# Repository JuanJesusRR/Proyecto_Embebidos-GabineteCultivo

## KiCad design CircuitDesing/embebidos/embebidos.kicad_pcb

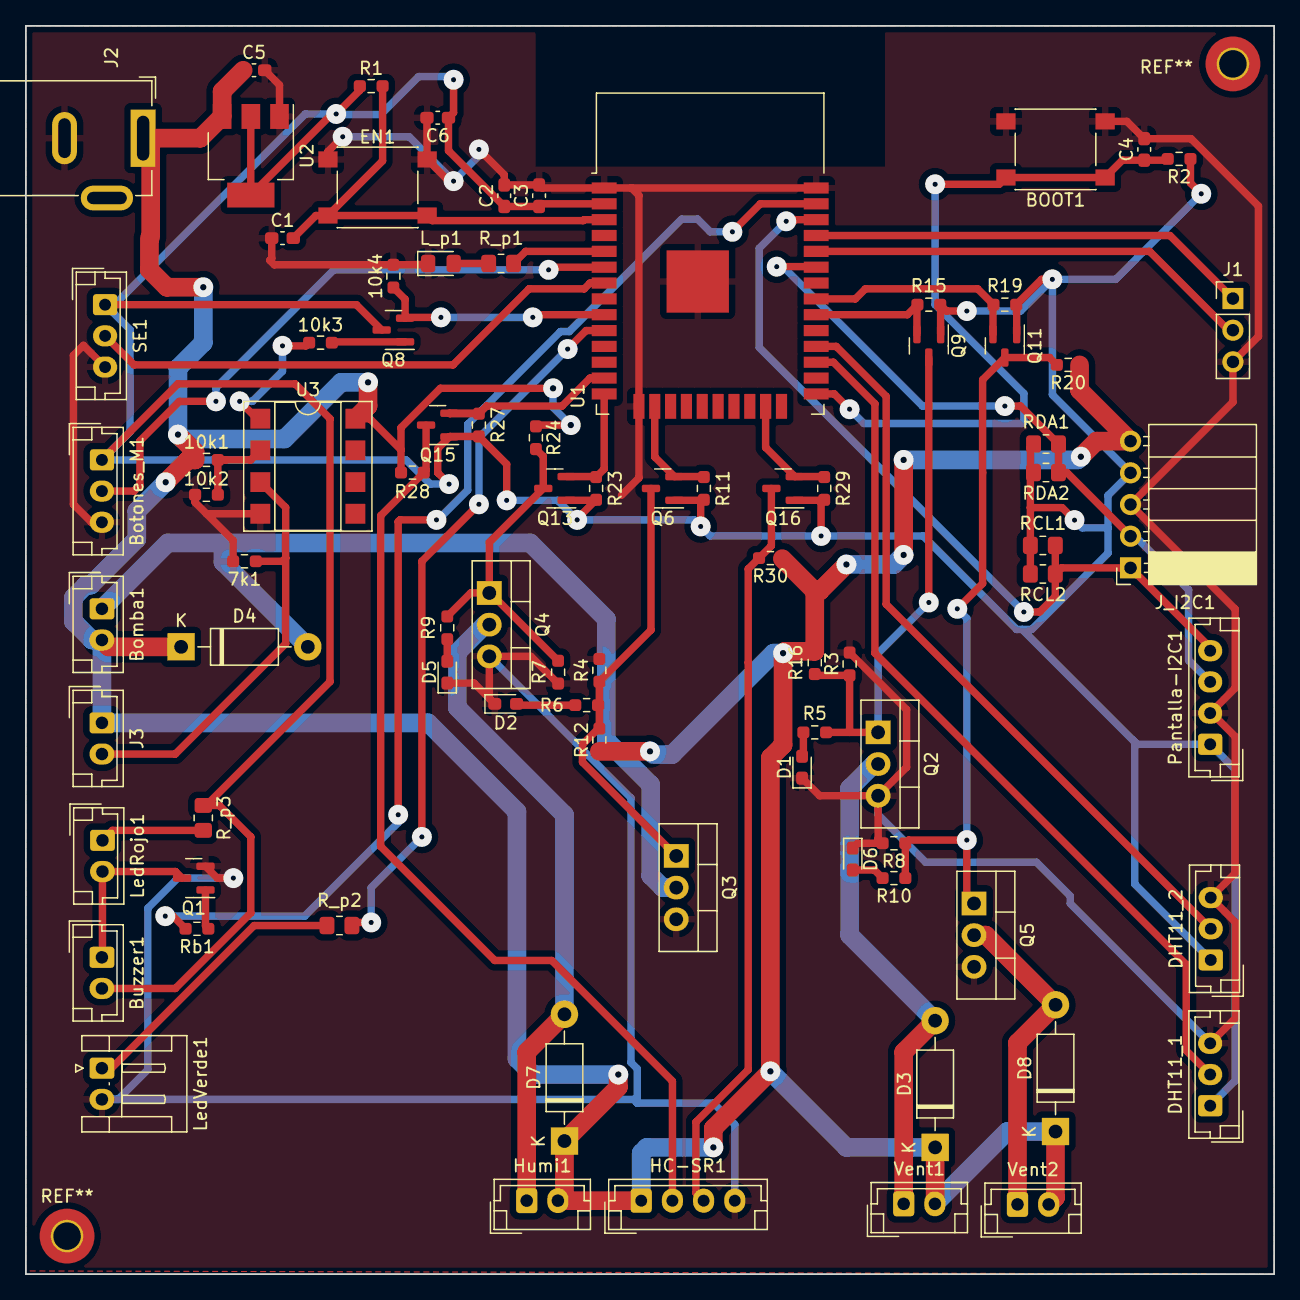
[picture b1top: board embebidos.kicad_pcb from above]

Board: 2 copper layers, 100.1 x 100.1 mm, 84 parts (0 on the bottom side), 46 nets.

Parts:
7k1, 10k1, 10k2, 10k3, 10k4: R; R_0603_1608Metric_Pad0.98x0.95mm_HandSolder
BOOT1: SW_Push; SW_Push_1P1T_NO_6x6mm_H9.5mm
Bomba1: Conn_01x02; JST_EH_B2B-EH-A_1x02_P2.50mm_Vertical
Botones_M1: Conn_01x03; JST_EH_B3B-EH-A_1x03_P2.50mm_Vertical
Buzzer1: Conn_01x02; JST_EH_B2B-EH-A_1x02_P2.50mm_Vertical
C1, C4: 1uF; C_0603_1608Metric_Pad1.08x0.95mm_HandSolder
C2: 0.1uF; C_0603_1608Metric_Pad1.08x0.95mm_HandSolder
C3: 10uF; C_0603_1608Metric_Pad1.08x0.95mm_HandSolder
C5: 10u; C_0603_1608Metric_Pad1.08x0.95mm_HandSolder
C6: 100u; C_0603_1608Metric_Pad1.08x0.95mm_HandSolder
D1, D2, D5, D6: LED; LED_0603_1608Metric_Pad1.05x0.95mm_HandSolder
D3, D4, D7, D8: 1N4004; D_DO-41_SOD81_P10.16mm_Horizontal
DHT11_1, DHT11_2: Conn_01x03; JST_EH_B3B-EH-A_1x03_P2.50mm_Vertical
EN1: SW_Push; SW_Push_1P1T_NO_6x6mm_H9.5mm
HC-SR1: Conn_01x04; JST_EH_B4B-EH-A_1x04_P2.50mm_Vertical
Humi1: Conn_01x02; JST_EH_B2B-EH-A_1x02_P2.50mm_Vertical
J1: Conn_01x03_Male; PinHeader_1x03_P2.54mm_Vertical
J2: Barrel_Jack; BarrelJack_GCT_DCJ200-10-A_Horizontal
J3: Conn_01x02; JST_EH_B2B-EH-A_1x02_P2.50mm_Vertical
J_I2C1: Conn_01x05_Male; PinSocket_1x05_P2.54mm_Horizontal
L_p1: LED; LED_0805_2012Metric_Pad1.15x1.40mm_HandSolder
LedRojo1: Conn_01x02; JST_EH_B2B-EH-A_1x02_P2.50mm_Vertical
LedVerde1: Conn_01x02; JST_EH_S2B-EH_1x02_P2.50mm_Horizontal
Pantalla-I2C1: Conn_01x04; JST_EH_B4B-EH-A_1x04_P2.50mm_Vertical
Q1, Q6, Q9, Q11, Q13, Q15, Q16: BSS138; SOT-23
Q2, Q3, Q4, Q5: IRF540N; TO-220-3_Vertical
Q8: MMBT3904; SOT-23
R1, R2, R11, R12, R15, R16, R19, R20, R23, R24, R27, R28, R29, R30: 10k; R_0603_1608Metric_Pad0.98x0.95mm_HandSolder
R3, R4, R5, R6, R7, R8, R9, R10: 1k; R_0603_1608Metric_Pad0.98x0.95mm_HandSolder
RCL1, RCL2: 10k; R_0805_2012Metric_Pad1.20x1.40mm_HandSolder
RDA1, RDA2: 10k; R_0805_2012Metric_Pad1.20x1.40mm_HandSolder
R_p1, R_p2: 47; R_0805_2012Metric_Pad1.20x1.40mm_HandSolder
R_p3: 1k; R_0805_2012Metric_Pad1.20x1.40mm_HandSolder
Rb1: 1k; R_0603_1608Metric_Pad0.98x0.95mm_HandSolder
SE1: Conn_01x03; JST_EH_B3B-EH-A_1x03_P2.50mm_Vertical
U1: ESP32-WROOM-32
U2: AMS1117-3.3; SOT-223-3_TabPin2
U3: LM4250; DIP-8_W7.62mm_SMDSocket_SmallPads
Vent1, Vent2: Conn_01x02; JST_EH_B2B-EH-A_1x02_P2.50mm_Vertical

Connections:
3.3v: Botones_M1.1, Buzzer1.2, C2.1, C3.1, C6.1, DHT11_1.1, DHT11_2.1, J_I2C1.4, Pantalla-I2C1.1, Q6.1 (G), Q8.3 (C), Q9.1 (G), Q11.1 (G), Q13.1 (G), Q15.1 (G), Q16.1 (G), R1.1, R2.1, R11.1, R15.1, R19.1, R23.1, R27.1, R29.1, RCL1.2, RCL2.2, RDA1.2, RDA2.2, R_p3.1, SE1.1, U1.2 (VDD), U2.2 (VO)
5v: 10k1.1, Bomba1.2, C5.1, D3.1 (K), D4.1 (K), D7.1 (K), D8.1 (K), HC-SR1.1, Humi1.2, J2.1, J3.1, J_I2C1.5, R12.1, R16.1, R20.1, R24.1, R28.1, R30.1, U2.3 (VI), U3.8 (IQ), Vent1.2, Vent2.2
/Actuadores/Conversor_NLog1/HV1: Q2.1 (G), Q9.3 (D), R3.1, R5.1, R16.2
/Actuadores/Conversor_NLog2/HV1: Q5.1 (G), Q11.3 (D), R8.1, R10.1, R20.2
/Actuadores/Conversor_NLog3/HV1: Q3.1 (G), Q6.3 (D), R4.1, R6.1, R12.2
/Actuadores/Conversor_NLog4/HV1: Q4.1 (G), Q13.3 (D), R7.1, R9.1, R24.2
/Botones: Botones_M1.2, U1.6 (IO34)
/Buzzer: Rb1.2, U1.37 (IO23)
/Esp32Schematic/BOOT: BOOT1.1, C4.1, R2.2, U1.25 (IO0)
/HC-SR04Echo: Q16.2 (S), R29.2, U1.23 (IO15)
/HC-SR04Trig: Q15.2 (S), R27.2, U1.13 (IO14)
/LedU1: R_p1.2, U1.5 (SENSOR_VN)
/Led_Verde: R_p2.2, U1.10 (IO25)
/Prog_Rx: J1.1, U1.35 (TXD0/IO1)
/Prog_Tx: J1.2, U1.34 (RXD0/IO3)
/Sensores/Conversor_NLog5/HV1: HC-SR1.2, Q15.3 (D), R28.2
/Sensores/Conversor_NLog5/HV2: HC-SR1.3, Q16.3 (D), R30.2
/c_bomba: Q6.2 (S), R11.2, U1.16 (IO13)
/c_hum: Q13.2 (S), R23.2, U1.14 (IO12)
/c_vent1: Q9.2 (S), R15.2, U1.30 (IO18)
/c_vent2: Q11.2 (S), R19.2, U1.31 (IO19)
/dht11_1d: DHT11_1.2, U1.27 (IO16)
/dht11_2d: DHT11_2.2, U1.28 (IO17)
/lm393_d: 10k4.1, Q8.2 (E), U1.9 (IO33)
/se093_d: SE1.2, U1.7 (IO35)
GND: 7k1.2, 10k2.2, 10k4.2, BOOT1.2, Botones_M1.3, C1.1, C2.2, C3.2, C4.2, C5.2, C6.2, D1.1 (K), D2.1 (K), D5.1 (K), D6.1 (K), DHT11_1.3, DHT11_2.3, EN1.1, HC-SR1.4, J1.3, J2.2, J_I2C1.3, L_p1.1 (K), LedVerde1.2, Pantalla-I2C1.2, Q1.2 (S), Q2.3 (S), Q3.3 (S), Q4.3 (S), Q5.3 (S), R3.2, R4.2, R7.2, R8.2, SE1.3, U1.1 (GND), U1.15 (GND), U1.38 (GND), U1.39 (GND), U2.1 (GND), U3.4 (V-)
unnamed: 7k1.1, J3.2, U3.3 (+)
unnamed: 10k1.2, 10k2.1, U3.2 (-)
unnamed: 10k3.1, U3.1 (NULL)
unnamed: 10k3.2, Q8.1 (B)
unnamed: Bomba1.1, D4.2 (A), Q3.2 (D)
unnamed: Buzzer1.1, LedRojo1.2, Q1.3 (D)
unnamed: C1.2, EN1.2, R1.2, U1.3 (EN)
unnamed: D1.2 (A), R5.2
unnamed: D2.2 (A), R6.2
unnamed: D3.2 (A), Q2.2 (D), Vent1.1
unnamed: D5.2 (A), R9.2
unnamed: D6.2 (A), R10.2
unnamed: D7.2 (A), Humi1.1, Q4.2 (D)
unnamed: D8.2 (A), Q5.2 (D), Vent2.1
unnamed: L_p1.2 (A), R_p1.1
unnamed: LedRojo1.1, R_p3.2
unnamed: LedVerde1.1, R_p2.1
unnamed: Q1.1 (G), Rb1.1
SCL: J_I2C1.1, Pantalla-I2C1.4, RCL1.1, RCL2.1, U1.36 (IO22)
SDA: J_I2C1.2, Pantalla-I2C1.3, RDA1.1, RDA2.1, U1.33 (IO21)

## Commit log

2022-09-12 Circuit Desing
    First Circuit Desing Schematic
2022-09-13 Avance esquemático
    Subcircuitos
2022-09-24 Potencia
    Primera propuesta del esquema de potencia
2022-09-27 Bootoption enable sw
2022-09-28 circuit
2022-10-05 LDR
    Comparacion LDR
2022-10-05 Sensor Ultrasonido
2022-10-06 Concatenación Buck - LDO
    .
2022-10-10 Huellas parciales
2022-10-10 15 footprints faltantes
2022-10-10 Todas las huellas
2022-10-11 pull up
    Circuito LDR
2022-10-16 Actualizacion huellas
    Huellas+Programador
2022-10-17 Coversores lógicos + alertas + humidificador
    Coversores lógicos + alertas + humidificador
2022-10-17 Cambio 3.3V en alertas
    Cambio 3.3V en alertas
2022-10-18 Ruteo completo
2022-10-20 Ruteo plano a tierra
2022-10-25 Jack, arreglos para disipacion
2022-11-27 Codigo Agregado
2022-11-30 Hello
    .
2022-11-30 Ventiladores
    .
2022-11-30 Vent 1
2022-11-30 .
    .
2022-11-30 Bomba
2022-11-30 Ultrasonido
    1
2022-11-30 DHT11
2022-12-01 Modularizacion del codigo
    Se agregaron nuevos modulos en el main actualmente se controla un ventilador con la temperatura
2022-12-01 Botones
    .
2022-12-01 pin 34
2022-12-01 Pantalla
2022-12-03 GitIgnore
2022-12-03 Comentario
2022-12-03 Sergio
2022-12-05 Integracion pantalla
2022-12-05 Ultima modificacion pantalla
2022-12-06 Create imagenes
2022-12-06 Funcionamiento Control
    Control de la humedad mediante los ventilador, humidificador y sensor de humedad y temperaturas
2022-12-07 Integracion Casi completa
2022-12-07 Integracion completa
2022-12-08 final
